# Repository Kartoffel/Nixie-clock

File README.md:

# Nixie-clock
DIY IN-14 Nixie clock

### Read the article at https://blankers.eu/2021/nixie-clock/

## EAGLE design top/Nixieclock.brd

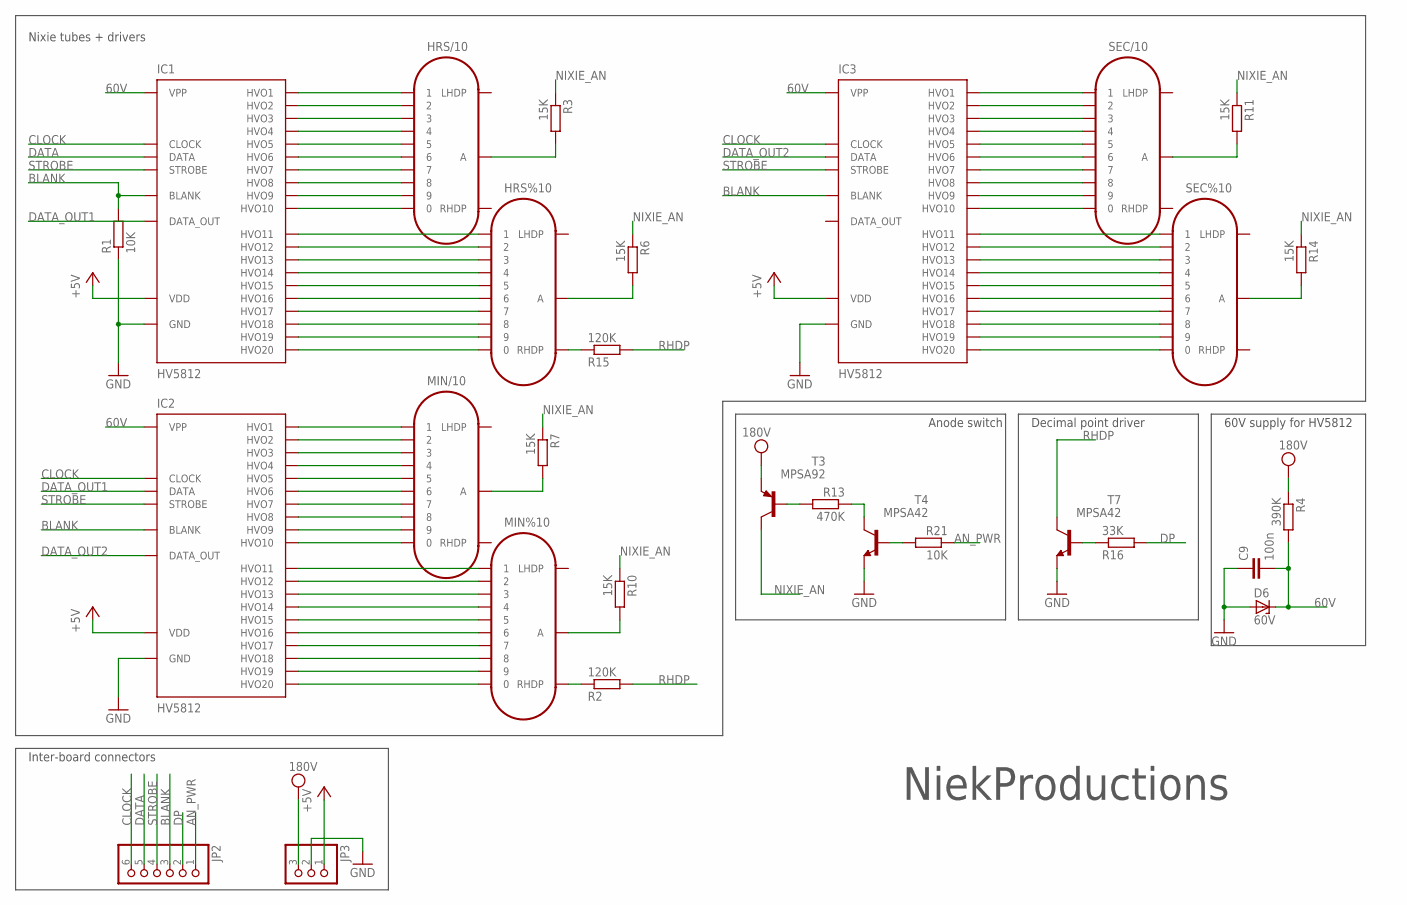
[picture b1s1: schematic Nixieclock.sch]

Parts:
C9: 100n; C025-025X050
D6: 60V; F126Z12
HRS%10: IN-14
HRS/10: IN-14
IC1, IC2, IC3: HV5812; PLCC-28-SMD
JP2: PINHD-1X6; 1X06
JP3: PINHD-1X3; 1X03
MIN%10: IN-14
MIN/10: IN-14
R1, R21: 10K; 0207/12
R2, R15: 120K; 0207/12
R3, R6, R7, R10, R11, R14: 15K; 0207/12
R4: 390K; 0207/12
R13: 470K; 0207/12
R16: 33K; 0207/12
SEC%10: IN-14
SEC/10: IN-14
T3: MPSA92; TO92-EBC
T4, T7: MPSA42; TO92-EBC
U$4: NPLOGO1CM-DIA; NPLOGO-1CM

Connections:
60V: C9.2, D6.C, IC1.1 (VPP), IC2.1 (VPP), IC3.1 (VPP), R4.2
+5V: IC1.28 (VDD), IC2.28 (VDD), IC3.28 (VDD), JP3.1
AN_PWR: JP2.1, R21.1
BLANK: IC1.13 (BLANK), IC2.13 (BLANK), IC3.13 (BLANK), JP2.3, R1.2
CLOCK: IC1.15 (CLOCK), IC2.15 (CLOCK), IC3.15 (CLOCK), JP2.6
DATA: IC1.27 (DATA), JP2.5
DATA_OUT1: IC1.2 (DATA_OUT), IC2.27 (DATA)
DATA_OUT2: IC2.2 (DATA_OUT), IC3.27 (DATA)
DP: JP2.2, R16.2
GND: C9.1, D6.A, IC1.14 (GND), IC2.14 (GND), IC3.14 (GND), JP3.2, R1.1, T4.E, T7.E
HVO1: HRS/10.1, IC1.26 (HVO1)
HVO2: HRS/10.2, IC1.25 (HVO2)
HVO3: HRS/10.3, IC1.24 (HVO3)
HVO4: HRS/10.4, IC1.23 (HVO4)
HVO5: HRS/10.5, IC1.22 (HVO5)
HVO6: HRS/10.6, IC1.21 (HVO6)
HVO7: HRS/10.7, IC1.20 (HVO7)
HVO8: HRS/10.8, IC1.19 (HVO8)
HVO9: HRS/10.9, IC1.18 (HVO9)
HVO10: HRS/10.0, IC1.17 (HVO10)
HVO20: IC2.3 (HVO20), MIN%10.0
unnamed: HRS%10.RHDP, R15.1
unnamed: MIN%10.RHDP, R2.1
unnamed: R16.1, T7.B
unnamed: R13.2, T3.B
unnamed: HRS/10.A, R3.2
unnamed: IC3.25 (HVO2), SEC/10.2
unnamed: IC3.23 (HVO4), SEC/10.4
unnamed: R13.1, T4.C
unnamed: R21.2, T4.B
unnamed: MIN/10.A, R7.2
unnamed: R11.2, SEC/10.A
unnamed: IC3.22 (HVO5), SEC/10.5
unnamed: HRS%10.A, R6.2
unnamed: IC3.21 (HVO6), SEC/10.6
unnamed: IC3.20 (HVO7), SEC/10.7
unnamed: IC3.19 (HVO8), SEC/10.8
unnamed: IC3.18 (HVO9), SEC/10.9
unnamed: IC3.17 (HVO10), SEC/10.0
unnamed: IC3.12 (HVO11), SEC%10.1
unnamed: IC3.11 (HVO12), SEC%10.2
unnamed: IC3.10 (HVO13), SEC%10.3
unnamed: IC3.9 (HVO14), SEC%10.4
unnamed: IC3.8 (HVO15), SEC%10.5
unnamed: IC3.7 (HVO16), SEC%10.6
unnamed: IC3.6 (HVO17), SEC%10.7
unnamed: IC3.5 (HVO18), SEC%10.8
unnamed: IC3.4 (HVO19), SEC%10.9
unnamed: MIN%10.A, R10.2
unnamed: IC3.24 (HVO3), SEC/10.3
unnamed: IC3.3 (HVO20), SEC%10.0
unnamed: IC3.26 (HVO1), SEC/10.1
unnamed: HRS%10.0, IC1.3 (HVO20)
unnamed: HRS%10.9, IC1.4 (HVO19)
unnamed: HRS%10.8, IC1.5 (HVO18)
unnamed: HRS%10.7, IC1.6 (HVO17)
unnamed: HRS%10.5, IC1.8 (HVO15)
unnamed: HRS%10.6, IC1.7 (HVO16)
unnamed: HRS%10.3, IC1.10 (HVO13)
unnamed: HRS%10.4, IC1.9 (HVO14)
unnamed: HRS%10.1, IC1.12 (HVO11)
unnamed: HRS%10.2, IC1.11 (HVO12)
unnamed: IC2.26 (HVO1), MIN/10.1
unnamed: IC2.25 (HVO2), MIN/10.2
unnamed: R14.2, SEC%10.A
unnamed: IC2.24 (HVO3), MIN/10.3
unnamed: IC2.23 (HVO4), MIN/10.4
unnamed: IC2.22 (HVO5), MIN/10.5
unnamed: IC2.21 (HVO6), MIN/10.6
unnamed: IC2.20 (HVO7), MIN/10.7
unnamed: IC2.19 (HVO8), MIN/10.8
unnamed: IC2.18 (HVO9), MIN/10.9
unnamed: IC2.17 (HVO10), MIN/10.0
unnamed: IC2.12 (HVO11), MIN%10.1
unnamed: IC2.11 (HVO12), MIN%10.2
unnamed: IC2.10 (HVO13), MIN%10.3
unnamed: IC2.9 (HVO14), MIN%10.4
unnamed: IC2.8 (HVO15), MIN%10.5
unnamed: IC2.7 (HVO16), MIN%10.6
unnamed: IC2.6 (HVO17), MIN%10.7
unnamed: IC2.5 (HVO18), MIN%10.8
unnamed: IC2.4 (HVO19), MIN%10.9
NIXIE_AN: R3.1, R6.1, R7.1, R10.1, R11.1, R14.1, T3.C
RHDP: R2.2, R15.2, T7.C
STROBE: IC1.16 (STROBE), IC2.16 (STROBE), IC3.16 (STROBE), JP2.4
VPP: JP3.3, R4.1, T3.E

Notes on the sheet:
Decimal point driver
Nixie tubes + drivers
Inter-board connectors
Anode switch
60V supply for HV5812

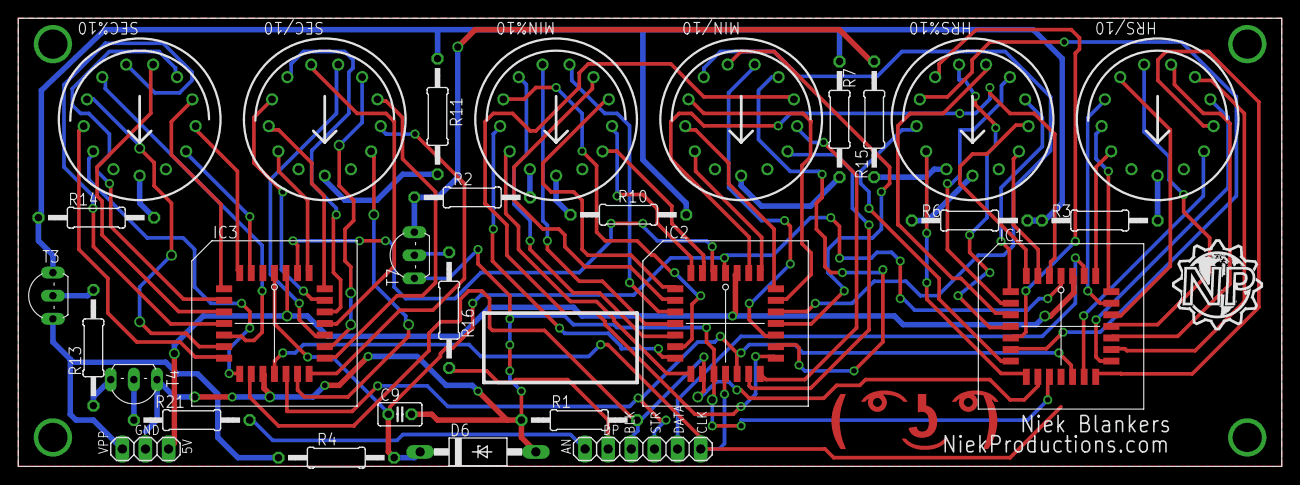
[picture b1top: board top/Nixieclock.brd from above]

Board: 2 copper layers, 138.7 x 49.2 mm, 31 parts (1 on the bottom side), 86 nets.

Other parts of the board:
U$5: LENNY

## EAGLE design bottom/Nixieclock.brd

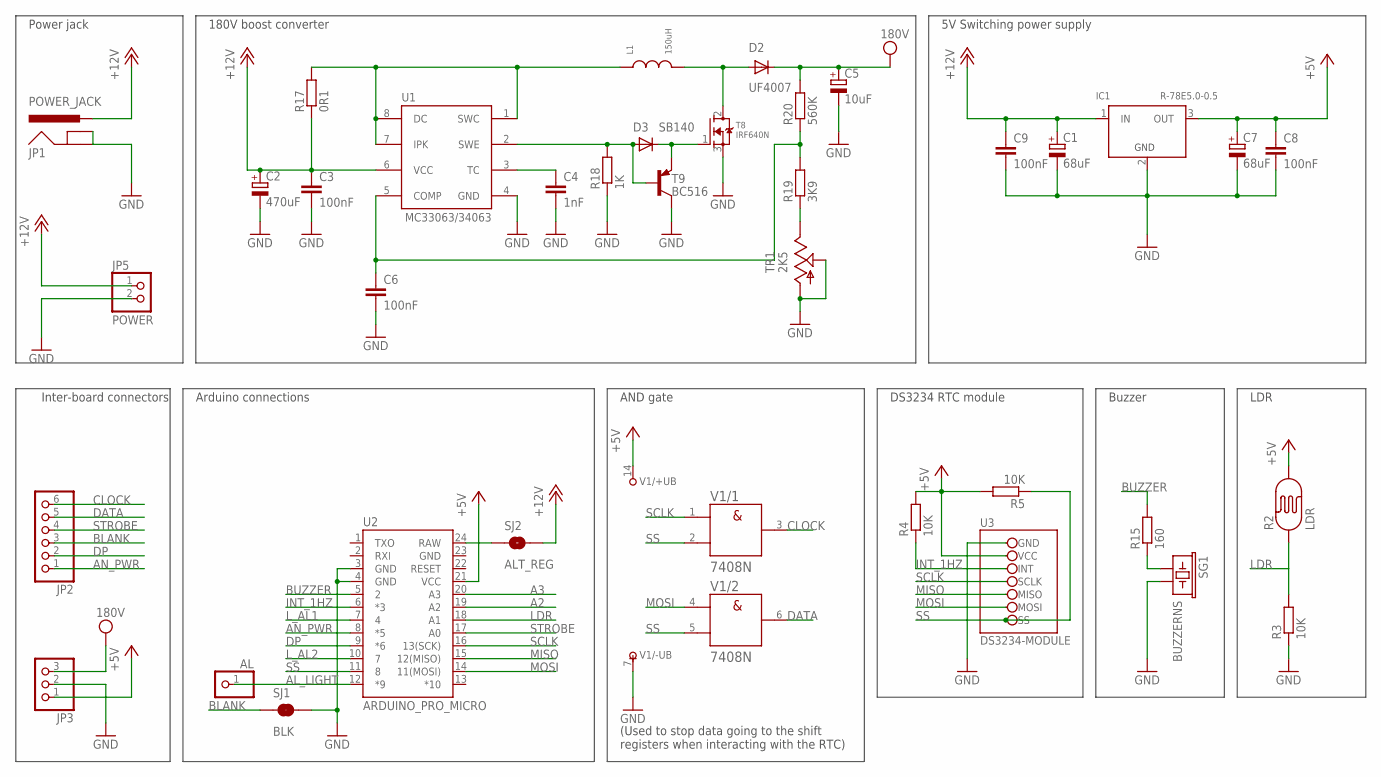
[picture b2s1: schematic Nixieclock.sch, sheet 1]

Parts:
AL: PINHD-1X1; 1X01
C1, C7: 68uF; E2,5-6
C2: 470uF; E5-10,5
C3, C6: 100nF; C025-024X044
C4: 1nF; C025-024X044
C5: 10uF; E5-10,5
C8, C9: 100nF; C025-025X050
D2: UF4007; DO41-10
D3: SB140; DO41-10
IC1: R-78E5.0-0.5; R-78E
JP1: POWER_JACK; POWER_JACK_PTH_LOCK
JP2: PINHD-1X6; 1X06
JP3: PINHD-1X3; 1X03
JP5: POWER; 1X02
L1: 150uH; INDUCTOR
R2: LDR; PHOTOCELL
R3, R4, R5: 10K; 0204/7
R15: 160; 0204/7
R17: 0R1; 0309/12
R18: 1K; 0207/10
R19: 3K9; 0207/10
R20: 560K; 0207/10
SG1: BUZZERNS; BUZZER-12MM-NS
SJ1: BLK; PAD-JUMPER-2-NC_BY_TRACE_YES_SILK
SJ2: ALT_REG; SJ_2S-NO
T8: IRF640N; TO220V
T9: BC516; TO92-EBC
TR1: 2K5; 6MM
U1: MC33063; DIL08
U2: ARDUINO_PRO_MICRO
U3: DS3234-MODULE; GEETECH-DS3234
V1: 7408N; DIL14

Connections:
+5V: C7.+, C8.1, IC1.3 (OUT), JP3.1, R2.2, R4.2, R5.2, U2.21 (VCC), U3.VCC, V1.14 (+UB); also elsewhere on the board
+12V: C1.+, C2.+, C3.1, C9.1, IC1.1 (IN), JP1.PWR, JP5.1, R17.1, SJ2.2, U1.6 (VCC)
A2: U2.19 (A2); also elsewhere on the board
A3: U2.20 (A3); also elsewhere on the board
AL_LIGHT: AL.1, U2.12 (*9)
AN_PWR: JP2.1, U2.8 (*5); also elsewhere on the board
BLANK: JP2.3, SJ1.1
BUZZER: R15.2, U2.5 (2)
CLOCK: JP2.6, V1.3 (Y)
DATA: JP2.5, V1.6 (Y)
DP: JP2.2, U2.9 (*6)
GND: C1.-, C2.-, C3.2, C4.2, C5.-, C6.2, C7.-, C8.2, C9.2, IC1.2 (GND), JP1.GND, JP1.GNDBREAK, JP3.2, JP5.2, R3.1, R18.1, SG1.- (2), SG1.-- (2), SJ1.2, T8.3 (S), T9.C, TR1.A, TR1.S, U1.4 (GND), U2.3 (GND), U2.4 (GND), U3.GND~1 (GND), U3.GND~2 (GND), V1.7 (-UB); also elsewhere on the board
INT_1HZ: R4.1, U2.6 (*3), U3.INT
LDR: R2.1, R3.2, U2.18 (A1)
L_AL1: U2.7 (4); also elsewhere on the board
L_AL2: U2.10 (7); also elsewhere on the board
MISO: U2.15 (12(MISO)), U3.MISO
MOSI: U2.14 (11(MOSI)), U3.MOSI, V1.4 (A)
unnamed: D3.A, R18.2, T9.B, U1.2 (SWE)
unnamed: D3.C, T8.1 (G), T9.E
unnamed: C4.1, U1.3 (TC)
unnamed: L1.P$1, R17.2, U1.1 (SWC), U1.7 (IPK), U1.8 (DC)
unnamed: D2.A, L1.P$2, T8.2 (D)
unnamed: C6.1, R19.2, R20.1, U1.5 (COMP)
unnamed: R19.1, TR1.E
unnamed: SJ2.1, U2.24 (RAW)
unnamed: R15.1, SG1.+ (1)
SCLK: U2.16 (13(SCK)), U3.SCLK, V1.1 (A)
SS: R5.1, U2.11 (8), U3.SS, V1.2 (B), V1.5 (B)
STROBE: JP2.4, U2.17 (A0)
VPP: C5.+, D2.C, JP3.3, R20.2; also elsewhere on the board

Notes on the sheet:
180V boost converter
Inter-board connectors
Power jack
5V Switching power supply
Arduino connections
LDR
AND gate
(Used to stop data going to the shift registers when interacting with the RTC)
Buzzer
DS3234 RTC module

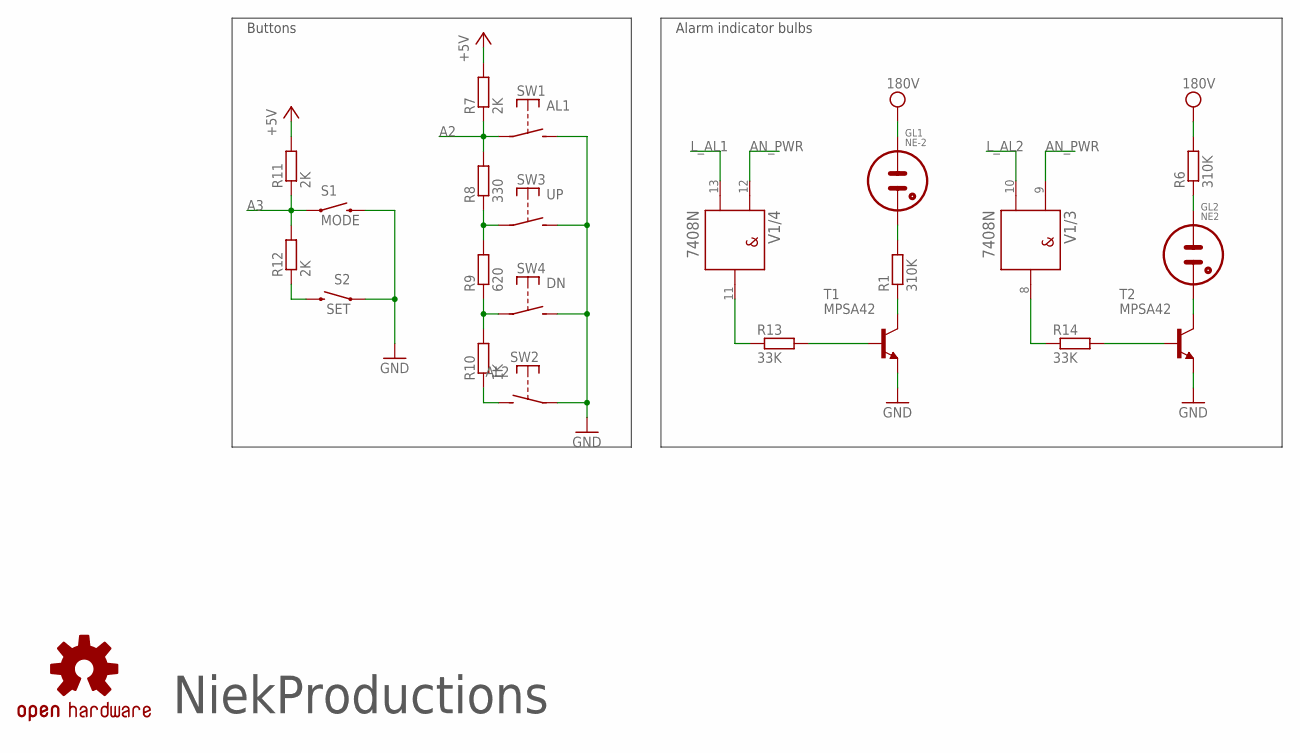
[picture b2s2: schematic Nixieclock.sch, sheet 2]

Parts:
GL1: NE-2; NE2-NEON-BULB-DRILL
GL2: NE2; NE2-NEON-BULB-DRILL
LOGO2: OSHW-LOGOL; OSHW-LOGO-L
R1: 310K; 0204V
R6: 310K; 0204/7
R7, R11, R12: 2K; 0204/7
R8: 330; 0204V
R9: 620; 0204V
R10: 1K; 0204V
R13, R14: 33K; 0204/7
S1: MODE; TACTILE-PTH-SIDEEZ
S2: SET; TACTILE-PTH-SIDEEZ
SW1: AL1; SW-12.65MM-SQ-WHITE
SW2: AL2; SW-12.65MM-SQ-WHITE
SW3: UP; SW-12.65MM-SQ-WHITE
SW4: DN; SW-12.65MM-SQ-WHITE
T1, T2: MPSA42; TO92-EBC
U$4: NPLOGO1CM-DIA; NPLOGO-1CM
V1: 7408N; DIL14

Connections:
+5V: R7.2, R11.2; also elsewhere on the board
A2: R7.1, R8.2, SW1.SW-CENTER; also elsewhere on the board
A3: R11.1, R12.2, S1.1; also elsewhere on the board
AN_PWR: V1.9 (A), V1.12 (A); also elsewhere on the board
GND: S1.2, S2.1, SW1.SW-OUTSIDE (S), SW2.SW-CENTER, SW3.SW-OUTSIDE (S), SW4.SW-OUTSIDE (S), T1.E, T2.E; also elsewhere on the board
L_AL1: V1.13 (B); also elsewhere on the board
L_AL2: V1.10 (B); also elsewhere on the board
unnamed: R13.2, T1.B
unnamed: R14.2, T2.B
unnamed: R12.1, S2.2
unnamed: R9.1, R10.2, SW4.SW-CENTER
unnamed: R8.1, R9.2, SW3.SW-CENTER
unnamed: R10.1, SW2.SW-OUTSIDE (S)
unnamed: R1.1, T1.C
unnamed: GL2.2 (A1), T2.C
unnamed: GL1.2 (A1), R1.2
unnamed: GL2.1 (A), R6.1
unnamed: R13.1, V1.11 (Y)
unnamed: R14.1, V1.8 (Y)
VPP: GL1.1 (A), R6.2; also elsewhere on the board

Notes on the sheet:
Alarm indicator bulbs
Buttons

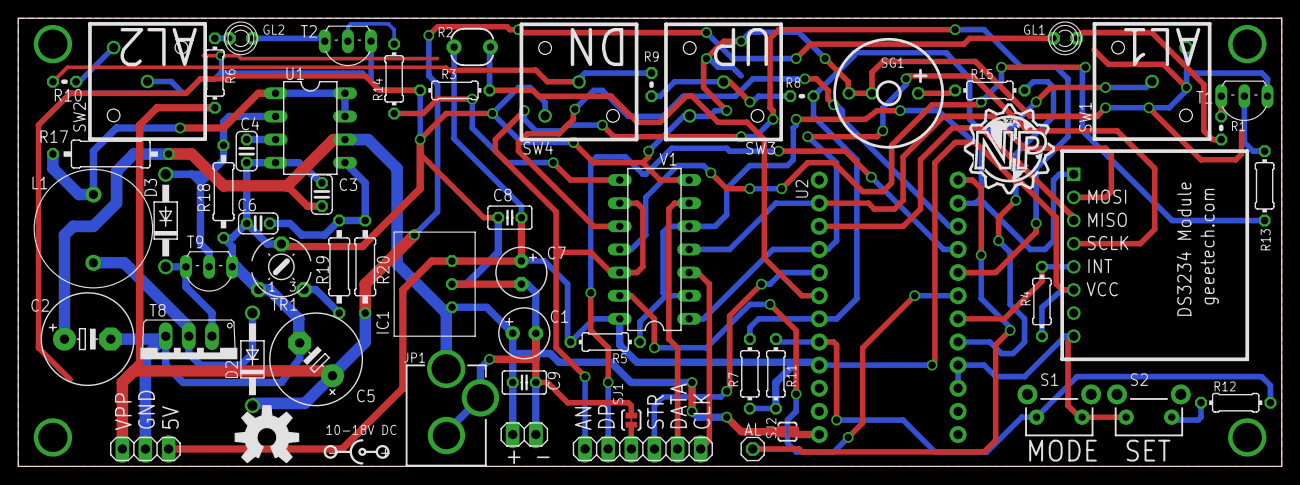
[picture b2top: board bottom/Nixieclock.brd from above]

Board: 2 copper layers, 138.7 x 49.2 mm, 59 parts (0 on the bottom side), 43 nets.

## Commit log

2015-06-23 Initial commit
    Design files, arduino code
2015-06-23 Updated schematic
2015-06-24 Improved readability, 80-character compatible
2015-07-05 Fixed alarm
2015-10-23 Alarm settings properly loaded
2015-10-23 Added automatic DST time adjustment
2016-12-06 Add pictures
2016-12-06 Add readme
2018-02-02 Add BOM

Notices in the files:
parts and their libraries:
SparkFun-Connectors: Licensing: Creative Commons ShareAlike 4.0 International - https://creativecommons.org/licenses/by-sa/4.0
